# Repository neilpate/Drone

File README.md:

# Drone

A learning project: build a quadcopter from scratch — own hardware, own firmware, no existing flight stack.

The drone is the artefact; understanding the whole stack end-to-end is the deliverable.

## What we're building

- **Platform:** BBC micro:bit v2 (nRF52833) for Phases 1–3; custom nRF5340 PCBA for Phases 4–5.
- **Language:** Rust (`no_std`, `embassy-nrf`) on the firmware; Rust on the PC-side ground-station application too.
- **IMU:** ICM-42688-P on SPI (external; micro:bit's onboard sensor has no gyro).
- **Airframe:** quadcopter.
- **Flight stack:** rolling our own — no PX4 / ArduPilot.

See [`doc/00-vision.md`](doc/00-vision.md) for the full vision and the phased milestone plan.

## Status

**Phase 2 (advanced prototyping) in progress.** The whole stack runs on hardware. The drone has made **first free flights** — brief untethered, self-levelling hops on its own battery under closed-loop control — with telemetry over a two-hop radio link and PID gains **tuned live from the ground station and now persisted to flash** ([ADR 0025](doc/decisions/0025-persist-control-parameters-flash.md)): tune, save, power-cycle, and the gains survive.

- **Round trip, ~100 Hz, ~25–30 ms.** The `groundstation` app sends four-axis pilot commands (sliders or a gamepad) over USB-CDC to a remote micro:bit, which relays to the drone over IEEE 802.15.4 ([ADR 0014](doc/decisions/0014-radio-protocol-ieee802154.md)). Telemetry returns the same path as a high/low-rate split frame ([ADR 0027](doc/decisions/0027-split-telemetry-high-low-rate.md)), postcard + COBS framed, every buffer sized at compile time from the shared types.
- **Firmware — an Embassy task graph.** A **supervisor** failsafe ([ADR 0017](doc/decisions/0017-supervisor-failsafe-state-machine.md)) is the sole publisher of motor commands: a five-state machine with a stick arm/disarm gesture, idle auto-disarm, and loss-of-link detection within ~100 ms.
- **Sense → estimate → control.** The ICM-42688-P IMU ([ADR 0003](doc/decisions/0003-imu-icm42688-spi.md)) is read over SPI at 1 kHz; a complementary filter ([ADR 0022](doc/decisions/0022-attitude-estimation-complementary-filter.md)) gives a roll/pitch estimate; a single-loop **angle-mode PID** ([ADR 0024](doc/decisions/0024-control-law-angle-mode-pd.md)) mixes it and the pilot command into a four-motor demand. IMU zeroing is re-runnable from the ground station; every gain is a runtime message, saveable to flash.
- **Actuation + ESC telemetry.** **DShot300** drives a 4-in-1 AM32 ESC ([parts list](hardware/electrical/parts-list.md)); each ESC's **KISS serial telemetry** — RPM, pack voltage, temperature — is read back over an idle-framed UART and logged.
- **Discipline.** Frames, signs and command newtypes are fixed in [ADR 0021](doc/decisions/0021-coordinate-frames-and-command-semantics.md); the pure logic (filter, controller, supervisor, wire types) is host-tested in `firmware-drone-core`.

The ground station plots and logs every signal live, times the round trip, pushes and saves PID gains, shows a live 3D view of the drone's attitude, and pairs with an offline `analyze` tool that turns a telemetry log into a legible flight report.

Recent tuning work — validating the integral term as a **centre-of-mass trim corrector**, balancing the airframe by the per-motor effort split, and re-zeroing out a one-directional drift — is consolidated into a new control-troubleshooting field guide ([doc/06-control-troubleshooting.md](doc/06-control-troubleshooting.md)).

**Phase 4 bring-up:** the custom nRF5340 flight controller (`drone_fc` v2, [ADR 0026](doc/decisions/0026-phase4-custom-pcba-nrf5340.md), [ADR 0028](doc/decisions/0028-fabricate-v2-board-pcbway.md)) is assembled, and **both cores now run the real firmware with the radio link working end to end**. The application core runs the flight-task port; the network core runs a raw 802.15.4 bridge; the two exchange frames over a hand-rolled shared-memory transport with IPC doorbells ([ADR 0029](doc/decisions/0029-multi-board-firmware-shared-library.md)). On hardware, the startup IPC loopback passes on both cores and command/telemetry traffic flows with the micro:bit remote. **Motor bench testing found a hardware fault on M1:** on the second board, the module's P0.03 (NFC2, pad 30) cannot be controlled — it reads high while driven low and does not drive the M1 net — while M2–M4 and P0.02 behave normally; the first board also shows an M1 fault (about 180 Ω to ground). Next: decide between module rework and moving M1 to a spare GPIO, raise the repeat same-pin failure with the vendor, then measure IPC round-trip latency and link-loss behavior, props off. See [hardware bring-up](hardware/electrical/README.md).

**Next (to finish Phase 2):** rebuild on the lighter next-generation frame — the previous flight frame was retired in a lost-control crash — with the IMU mounted near the centre of mass (which should cut the estimator lag at its source) and a fresh, softer re-tune; plus a firmware **power-limit** mode and the netted test enclosure ([doc/07-safety.md](doc/07-safety.md)). The micro:bit remains the tuning platform in parallel.

See [`doc/progress.md`](doc/progress.md) for the dated milestone history, [`doc/dev-environment.md`](doc/dev-environment.md) for the toolchain, and [`doc/decisions/`](doc/decisions/README.md) for the full decision history.

## Repository layout

- [`AGENTS.md`](AGENTS.md) — shared context file for AI coding assistants (Copilot, Claude, etc.). Read first.
- [`crates/`](crates/README.md) — Cargo workspace. `firmware-drone-microbit` (on-target binary), `firmware-drone-shared` (board-agnostic tasks/signals), and `firmware-drone-core` (host-testable logic).
- [`doc/`](doc/README.md) — design notes, vision, architecture, hardware/software/control docs.
- [`doc/02-architecture.md`](doc/02-architecture.md) — system architecture overview (two micro:bits, RF link, ground-station evolution).
- [`doc/decisions/`](doc/decisions/README.md) — Architecture Decision Records (ADRs).
- [`hardware/`](hardware/README.md) — mechanical (Fusion 360) and electrical (KiCad).

## Testing

Host-testable logic (wire types, the supervisor state machine, the ground-station helpers) is unit-tested and run with [cargo-nextest](https://nexte.st/):

```sh
cargo nextest run                                                 # workspace host crates
cargo nextest run --manifest-path crates/groundstation/Cargo.toml # the GUI crate
```

A tracked `pre-push` git hook runs the suite before every push, and [GitHub Actions](.github/workflows/ci.yml) runs `fmt` + `clippy` + tests on every push and pull request (the badge above). On-target firmware is exercised on hardware, not in CI. See [`doc/ci-and-testing.md`](doc/ci-and-testing.md) for the details and the one-time hook setup.

## Decisions so far

- [ADR 0001](doc/decisions/0001-platform-airframe-stack.md) — Real-hardware quadcopter, roll our own firmware, learning-first scope.
- [ADR 0002](doc/decisions/0002-mcu-and-language.md) — BBC micro:bit v2 + Rust for Phases 1–3.
- [ADR 0003](doc/decisions/0003-imu-icm42688-spi.md) — External IMU: ICM-42688-P on SPI.
- [ADR 0004](doc/decisions/0004-concurrency-embassy-channels.md) — Concurrency model: Embassy + channel-based actor pattern, no BSP.
- [ADR 0005](doc/decisions/0005-pc-software-language-rust.md) — PC-side software in Rust; shared `proto` crate for the wire protocol.
- [ADR 0006](doc/decisions/0006-mechanical-cad-fusion360.md) — Mechanical CAD: Fusion 360; commit `.f3d` source + `.stl` mesh (STEP dropped, amended 2026-07-09).
- [ADR 0007](doc/decisions/0007-testing-and-ci-strategy.md) — Testing and CI: unit-test everything possible, local-first feedback, `core`/`task` split, HIL deferred.
- [ADR 0008](doc/decisions/0008-repository-folder-layout.md) — Repository folder layout: `crates/`, `doc/`, `hardware/{mechanical,electrical}/`, all lowercase.
- [ADR 0009](doc/decisions/0009-workspace-bootstrap-and-crate-naming.md) — Workspace bootstrap from day one; `firmware-<role>` naming; `core`/`task` split realised as sibling crates.
- [ADR 0010](doc/decisions/0010-board-support-package.md) — Board Support Package layer: `board` module inside `firmware-drone`, Cargo-feature-selected, tasks take erased types.
- [ADR 0011](doc/decisions/0011-task-tracking-issues-and-batches.md) — Task tracking: GitHub Issues as canonical backlog, Projects board as view, labels as taxonomy, batched filing.
- [ADR 0012](doc/decisions/0012-lint-and-format-policy.md) — Lint and format policy: `main` stays `rustfmt`-clean and `clippy`-clean; suppressions require justification.
- [ADR 0013](doc/decisions/0013-async-communication-primitives.md) — Async inter-task communication: 2×2 rule over `Channel` / `Watch` / `Signal` / `PubSubChannel`.
- [ADR 0014](doc/decisions/0014-radio-protocol-ieee802154.md) — Radio link: IEEE 802.15.4 (raw PHY/MAC), channel 20.
- [ADR 0015](doc/decisions/0015-host-testing-no-std-crates.md) — Host-testable `no_std` crates: `cfg_attr(not(test), no_std)`, inline `mod tests`, `cargo test` honours `default-members`.
- [ADR 0016](doc/decisions/0016-newtype-per-physical-quantity.md) — Newtype per physical quantity for shared types: distinct newtypes per quantity, no shared `PercentageValue` base.
- [ADR 0017](doc/decisions/0017-supervisor-failsafe-state-machine.md) — Supervisor task as failsafe state machine: 4-state enum, tick-driven, pure logic in `firmware-drone-core`, supervisor is the sole publisher of motor commands.
- [ADR 0018](doc/decisions/0018-pc-link-uart-postcard-cobs.md) — PC ground-station link: USB-CDC virtual COM port to nRF52833 UART, 115 200 8N1, postcard + COBS framing (Proposed; first cut shipped with plain ASCII).
- [ADR 0019](doc/decisions/0019-airframe-class-3in-4s-printed.md) — Airframe and propulsion class: 3" ducted cinewhoop, 4S LiPo, 1507-class motors, DShot 4-in-1 ESC, fully 3D-printed PETG frame (Proposed).
- [ADR 0020](doc/decisions/0020-telemetry-aggregator-single-publisher.md) — Telemetry aggregator: a dedicated task is the sole publisher of `TelemetryState`, tick-sampling per-source `Watch`es at 100 Hz and owning frame-level fields.
- [ADR 0021](doc/decisions/0021-coordinate-frames-and-command-semantics.md) — Coordinate frames and command semantics: world NED + body FRD, right-hand sign conventions, angle (self-levelling) mode first, remote sends raw normalised stick deflections (Proposed).
- [ADR 0022](doc/decisions/0022-attitude-estimation-complementary-filter.md) — Attitude estimation: complementary filter for roll and pitch (fixed-gain accel/gyro blend); yaw stays rate-only; pure filter in `firmware-drone-core` (Proposed).
- [ADR 0023](doc/decisions/0023-motor-numbering-layout-rotation.md) — Motor numbering, layout, and rotation directions: quad-X, Betaflight numbering (M1 rear-right … M4 front-left), props-out rotation, with the derived mixer sign table (Proposed).
- [ADR 0024](doc/decisions/0024-control-law-angle-mode-pd.md) — Control law: single-loop PD per axis, angle mode for roll/pitch and rate mode for yaw, derivative on the measured gyro; a single-publisher controller stage the supervisor mixes in Armed (Proposed).
- [ADR 0025](doc/decisions/0025-persist-control-parameters-flash.md) — Persist control parameters to flash: log-structured parameter store in internal flash, disarmed-gated save-on-command from the ground station (Accepted).
- [ADR 0026](doc/decisions/0026-phase4-custom-pcba-nrf5340.md) — Phase 4 custom PCBA: nRF5340 module on a hand-designed KiCad carrier (Proposed).
- [ADR 0027](doc/decisions/0027-split-telemetry-high-low-rate.md) — Split telemetry into high-rate and low-rate frames: fast flight data + slower housekeeping (Proposed).
- [ADR 0028](doc/decisions/0028-fabricate-v2-board-pcbway.md) — Fabricate the v2 flight-controller board: turnkey PCBA on PCBWay (Proposed).

## Licence

Dual-licensed under either of:

- Apache License, Version 2.0 ([LICENSE-APACHE](LICENSE-APACHE) or <http://www.apache.org/licenses/LICENSE-2.0>)
- MIT license ([LICENSE-MIT](LICENSE-MIT) or <http://opensource.org/licenses/MIT>)

at your option.

Unless you explicitly state otherwise, any contribution intentionally submitted for inclusion in this work, as defined in the Apache-2.0 license, shall be dual-licensed as above, without any additional terms or conditions.

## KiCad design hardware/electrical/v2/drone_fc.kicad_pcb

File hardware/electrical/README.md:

# hardware/electrical/

Electrical and electronic design: schematics, PCB layout, fabrication outputs, wiring diagrams.

## SWD probe bench test

The [Pico SWD probe bring-up note](swd-probe-bringup.md) records the investigation
and links the preserved scope screenshot and raw waveform data.

The host-only Rust tool [swd-test](../../crates/swd-test/src/main.rs) checks outgoing
SWD electrical activity with the target board **disconnected**. It uses only the
standard library and calls the installed `probe-rs` executable.

- Connect CH1 to SWCLK, CH2 to SWDIO, and both probe grounds to probe-board GND.
- Match the scope's attenuation settings to the physical probe switches.
- Defaults: Rigol DHO804 at `192.168.2.30:5555`, CMSIS-DAP probe selector
  `2e8a:000c:E66594D0637D4534`. Optional positional arguments override these.
- Run from the repository root:
  `cargo run --manifest-path crates/swd-test/Cargo.toml`.
- The tool changes channel scales/coupling, timebase, acquisition, and trigger
  settings, captures both channels, and leaves the scope stopped.
- It checks low/high levels (1st/99th percentiles) against 3.3 V logic
  thresholds, transitions on both lines, and median SWCLK frequency against
  100 kHz (+/-20%), with at least 20 samples per period. SWDIO levels are
  measured over the clock-active window so long idle periods do not mask bits.
- It samples SWDIO on SWCLK rising edges and verifies the initial sequence:
  at least 50 high clocks, JTAG-to-SWD selection `0xE79E` (LSB first), another
  at least 50 high clocks, at least two low idle clocks, then DPIDR read request
  `0xA5` with valid start, stop, park, and even parity bits.
  Exit code 0 means all electrical and initial-sequence checks passed.
- A `probe-rs` no-target error is expected. A passing electrical test does not
  verify later transfers, target connectivity, or the absence of brief
  overshoot/ringing. The ACK-slot value is reported but is not a target
  acknowledgement with the target disconnected. Inspect edges on the scope
  separately.
- Validate the tool with `cargo test --manifest-path crates/swd-test/Cargo.toml`
  and `cargo clippy --manifest-path crates/swd-test/Cargo.toml --all-targets -- -D warnings`.

## Electrical design files

### Application-core firmware

The [nRF5340 app crate](../../crates/firmware-drone-nrf5340-app/Cargo.toml)
is a workspace member (ADR 0029) but builds separately from micro:bit firmware. It selects the
`nrf5340-app-s` Embassy HAL feature and targets the secure application core
with `thumbv8m.main-none-eabihf`.
Do not build it together with the micro:bit firmware: Cargo combines dependency
features within one build, and the two Embassy chip features are incompatible.
The repository's VS Code rust-analyzer settings focus on the app and scope
build-script and Clippy checks to it. The micro:bit and groundstation require
separate editor configuration when working on them.
Run Cargo from `crates/firmware-drone-nrf5340-app` so its local target/linker
configuration is loaded: `cargo build`, then `cargo clippy --bin firmware-drone-nrf5340-app -- -D warnings`.
The app starts the external high-frequency crystal and creates the BSP and
flight tasks. Before spawning tasks, it checks the radio-core IPC loopback.
Embassy's default debug configuration allows access and may write UICR
to disable application and secure debug protection. P0.03 is configured as
GPIO rather than NFC for motor M1. The app BSP hands P0.31 (the radio LED) to
the network core in `Board::new`, consuming its pin singleton so no app-core
driver can claim it.
`cargo run` requires probe-rs 0.32.0 or later on PATH, selects
`nRF5340_xxAA_APPONLY`, and flashes via the Pico at 100 kHz.
probe-rs 0.30.0 has a known nRF53 recovery bug (upstream PR 3701).
The app-only target avoids accessing the network core over SWD.
Board power and a stable TC2050 contact are required.

For the bare-metal motor-pin bench test, disconnect the ESC and power the board
separately. Run `cargo run --example motor-gpio-test` from the app crate. It
disables NFCT and drives M1 (P0.03) low then high, about 2 s each, with the
input buffer connected. The status LED shows the value read back from the pin,
so it should alternate in step with the drive; M1 should measure about 0 V and
3.3 V. If UICR still selects NFC pins, the LED stays on and the pins are not
configured. The test restores the UICR debug-protection settings at startup
without modifying UICR. Flash the normal app to restore DShot operation.

The v2 IMU mounting requires a 180-degree rotation about Y into the FRD body
frame: `(body_x, body_y, body_z) = (-sensor_x, sensor_y, -sensor_z)`, for both
accelerometer and gyro. Bench tilt and rotation checks confirmed this mapping
on 2026-11-12. The app BSP applies it during byte conversion, before calibration
or estimation. Level and stationary should read approximately `(0, 0, -1)` g.

The app status LED on P0.28 is active-high: the PCB connects its anode to the
GPIO and its cathode through a resistor to ground. It starts off and displays
the supervisor-state blink pattern. Repeated publications of the same state
do not restart the pattern; only a different state interrupts it.

### Network-core radio bridge

The [radio crate](../../crates/firmware-drone-nrf5340-radio/Cargo.toml) selects
the `nrf5340-net` Embassy feature and the `thumbv8m.main-none-eabi` Rust target
(the network core has no FPU). Build it separately from the other firmware by
running `cargo build` from `crates/firmware-drone-nrf5340-radio`. Its ELF links
to network flash at `0x01000000`. Its runner selects the full
`nRF5340_xxAA` target and the Pico probe; network-core debug access and flashing
were verified with the previous LED smoke-test images. The current image is
a raw 802.15.4 payload bridge; it depends on `nrf5340-ipc` but has no postcard
or `firmware-types` dependency. Its `board` module (`src/board.rs`) owns the
clock setup, radio interrupt binding and pin map, and exposes the radio, the
status LED on P0.31 and an `AppCoreInterface` wrapping the IPC endpoint. The
entry point creates the board and independently spawns `tasks::status_led` and
`tasks::remote_link`. The LED is a heartbeat, not an IPC-readiness indicator.
The remote-link task bridges raw payloads; startup probes from the app are
answered inside `nrf5340-ipc` and never reach it. Each task lives in its own
file under the radio crate's `src/tasks/`.

### Inter-core radio transport

Implemented 2026-11-12; **working on hardware**. After a power-cycle both LEDs
blink, the app logs `radio-core IPC loopback passed`, the network core logs
`app-core IPC probe answered`, and command/telemetry traffic flows with the
micro:bit remote on channel 20. Network was flashed first, then app, using
probe-rs 0.32.0 without chip-wide recovery. Both cores build and pass Clippy
separately; the queue has host tests:
`cargo test -p nrf5340-ipc` and
`cargo clippy -p nrf5340-ipc --all-targets -- -D warnings`.

- The concrete app BSP `RadioCoreInterface` lives alongside the other wrappers
  in `src/board/nrf5340.rs` and wraps `nrf5340-ipc`; the radio BSP's
  `AppCoreInterface` is its network-core counterpart. The micro:bit
  implementation is unchanged. Postcard and command dispatch stay on the app
  core; Embassy's radio `Packet` stays on the network core.
- Both linkers reserve `0x20070000..0x20080000`. The first 1076 bytes contain
  a version/magic word and two four-slot SPSC queues. Each slot contains a
  length and up to 125 payload bytes, packed into atomic `u32` words. The PHY
  header, CRC and LQI are not sent through IPC.
- The app holds the network core off, configures SPU RAM regions 56--63 as
  non-secure read/write, initializes both queues, configures IPC and releases
  the network core. The network domain is non-secure; no access to the rest of
  the app's RAM is granted. Both binaries check the linker region and the
  shared layout size.
- IPC channel/event 0 is reserved on both cores. A doorbell follows each
  enqueue/dequeue. Acquire/release publication and a `DMB` before notification
  order memory accesses. The interrupt wakes the local async waiter; the
  queue, not the event bit, determines whether data is available.
- At startup the app sends `drone-ipc-v1` through the real frame queues and
  waits up to two seconds for the echo. On success the app logs
  `radio-core IPC loopback passed`; a mismatch or timeout stops app startup.
  The network
  core has no startup phase or timeout: `nrf5340-ipc`'s network-side
  `Endpoint::receive` echoes the probe whenever one arrives (logging
  `app-core IPC probe answered`) and returns only other frames. Both halves of
  the handshake live in `nrf5340-ipc`; the probe bytes are private to it. Both
  log lines were observed on hardware on 2026-11-12.
- `receive()` returns the actual frame length and is cancellation-safe.
  `send()` means **queued**, not successfully transmitted over the air.
  A full app-to-net queue waits at most 50 ms; oversize payloads fail
  explicitly. A full net-to-app queue drops the incoming frame with a warning
  rather than blocking outgoing radio traffic. On-air send errors are logged
  on the network core; IPC does not add retries or delivery guarantees.
- Chip-temperature sampling was removed from the app. It logs the absence
  and seeds temperature with NaN, keeping the unchanged sensors aggregator
  and telemetry schema live without inventing a measurement.

Before hardware testing, disconnect motors or remove propellers. Use matching
app and network images, then cold-boot both cores; do not combine this app
with the old network LED-only image. An independent network-core reset or
reflash reattaches to the existing queues without panicking, and frames sent
by the app while it was down may be transmitted late. The app does not
re-probe, so restart the app (or power-cycle) to re-run the startup check.
A startup failure leaves the BSP's continuous motor
STOP frames running but does not verify physical motor behavior.

Remaining hardware acceptance: measure round-trip latency through the extra
IPC hop and test link-loss behavior props-off. Working command/telemetry
traffic is not flight-readiness evidence.

### Running each core

From the relevant crate directory, `cargo r` builds, flashes and monitors that
core with defmt RTT:

```powershell
cd crates\firmware-drone-nrf5340-app
cargo r
```

Or, starting from the repository root:

```powershell
cd crates\firmware-drone-nrf5340-radio
cargo r
```

The app uses the application-only probe-rs target; the radio uses the full
two-core target. Both runners were tested with the previous smoke-test images:
each printed its own boot message, and both images verified unchanged after
running the other core. Both LEDs blinked after a subsequent cold boot.
The current IPC/radio images were verified on hardware on 2026-11-12. Stop the
RTT monitor with Ctrl+C.

The radio runner requires a working app image to start and release the network
core. If probe-rs reports core 1 locked, check that the board is powered, the
app is running, and the TC2050 has good contact. Do not automatically grant an
erase: that message alone does not establish why access is unavailable.

### Flashing without an RTT console

The following Windows PowerShell commands build and flash one image at a time
using the Pico probe. They verify the written image and do not request a
chip-wide erase or permission to recover locked cores. Run from the repository
root. Only run `probe-rs download` if `cargo build` succeeds:

```powershell
cd crates\firmware-drone-nrf5340-app
cargo build
probe-rs download --chip nRF5340_xxAA_APPONLY --probe 2e8a:000c:E66594D0637D4534 --protocol swd --speed 100 --verify ..\..\target\thumbv8m.main-none-eabihf\debug\firmware-drone-nrf5340-app
```

For the network core, start from the repository root again:

```powershell
cd crates\firmware-drone-nrf5340-radio
cargo build
probe-rs download --chip nRF5340_xxAA --probe 2e8a:000c:E66594D0637D4534 --protocol swd --speed 100 --verify ..\..\target\thumbv8m.main-none-eabi\debug\firmware-drone-nrf5340-radio
```

After flashing either image, release the probe and power-cycle the board. The
app must run and release the network core before full-target access can work.
App flashing followed by verification of the unchanged network image, and
network flashing followed by verification of the unchanged app image, were
tested on the board. The TC2050 contact is intermittent: if SWD fails during
flashing, re-establish contact and verify or reflash the affected image.

The full target can report a core as locked when its debug access port is
unavailable. Recovery with `--allow-erase-all` can erase either core's image;
restore both images if recovery reports both cores locked. Do not use a
chip-wide erase to work around an access failure without first diagnosing it.
`probe-rs download` is distinct from `cargo run`: it does not start an RTT
console.

**Primary content (Phase 4 onwards):** custom nRF5340 carrier-board PCBA — the successor to the BBC micro:bit v2 for Phases 4–5 ([ADR 0002](../../doc/decisions/0002-mcu-and-language.md)).

**Tool:** KiCad (assumed, not yet ADR'd — decision lands with the Phase 4 PCBA design ADR).

**Expected committed file types:**

- `*.kicad_pro`, `*.kicad_sch`, `*.kicad_pcb`, `*.kicad_sym`, `*.kicad_mod` — KiCad project, schematic, board, symbol library, footprint library.
- `*.step` — 3D export of the assembled board, for mechanical fit checks against `hardware/mechanical/`.
- Fabrication outputs (Gerbers, drill files, BOM, pick-and-place) under a `fab/` subfolder per board revision, generated on tag.

**Naming:** by board, e.g. `flight-controller-rev-a/`, `flight-controller-rev-b/`. New revision = new folder, never overwrite.

## v2 Module Symbol

The custom `MDBT53_P1M` symbol in [v2/drone_fc_v2_symbols.kicad_sym](v2/drone_fc_v2_symbols.kicad_sym) includes all 65 module pads, checked against the [Raytac Rev. E datasheet](../../doc/hardware/%5BnRF5340%5D%20MDBT53-1M%20%26%20MDBT53-P1M_Ver.E%20spec.pdf), section 2.5 (pages 15-18). (2026-09-05)

- U3A retains the existing wired pin positions; U3B exposes the remaining GPIO; U3C exposes the regulator connections. These are units of one physical module, not separate components.
- GPIO pins use manufacturer names and bidirectional electrical types. Application functions belong on schematic net labels, not in the library pin names. Refer to the datasheet for fixed alternate functions such as analog inputs, NFC, crystal, QSPI, and high-speed SPI.
- Every unused pad has an explicit schematic no-connect. U3C follows normal-voltage LDO mode (section 8.1.1): VDD and VDDH are tied to 3.3 V, and DCCH, DCCD, DECD, DCC, and DECR are unconnected. Firmware must not enable DC/DC without the required external circuit.
- The library and schematic copies are synchronised. All pre-existing electrical connections were preserved when completing the symbol. The PCB and manufacturing outputs were not updated; the earlier schematic LED polarity correction remains separate from the manufactured board.

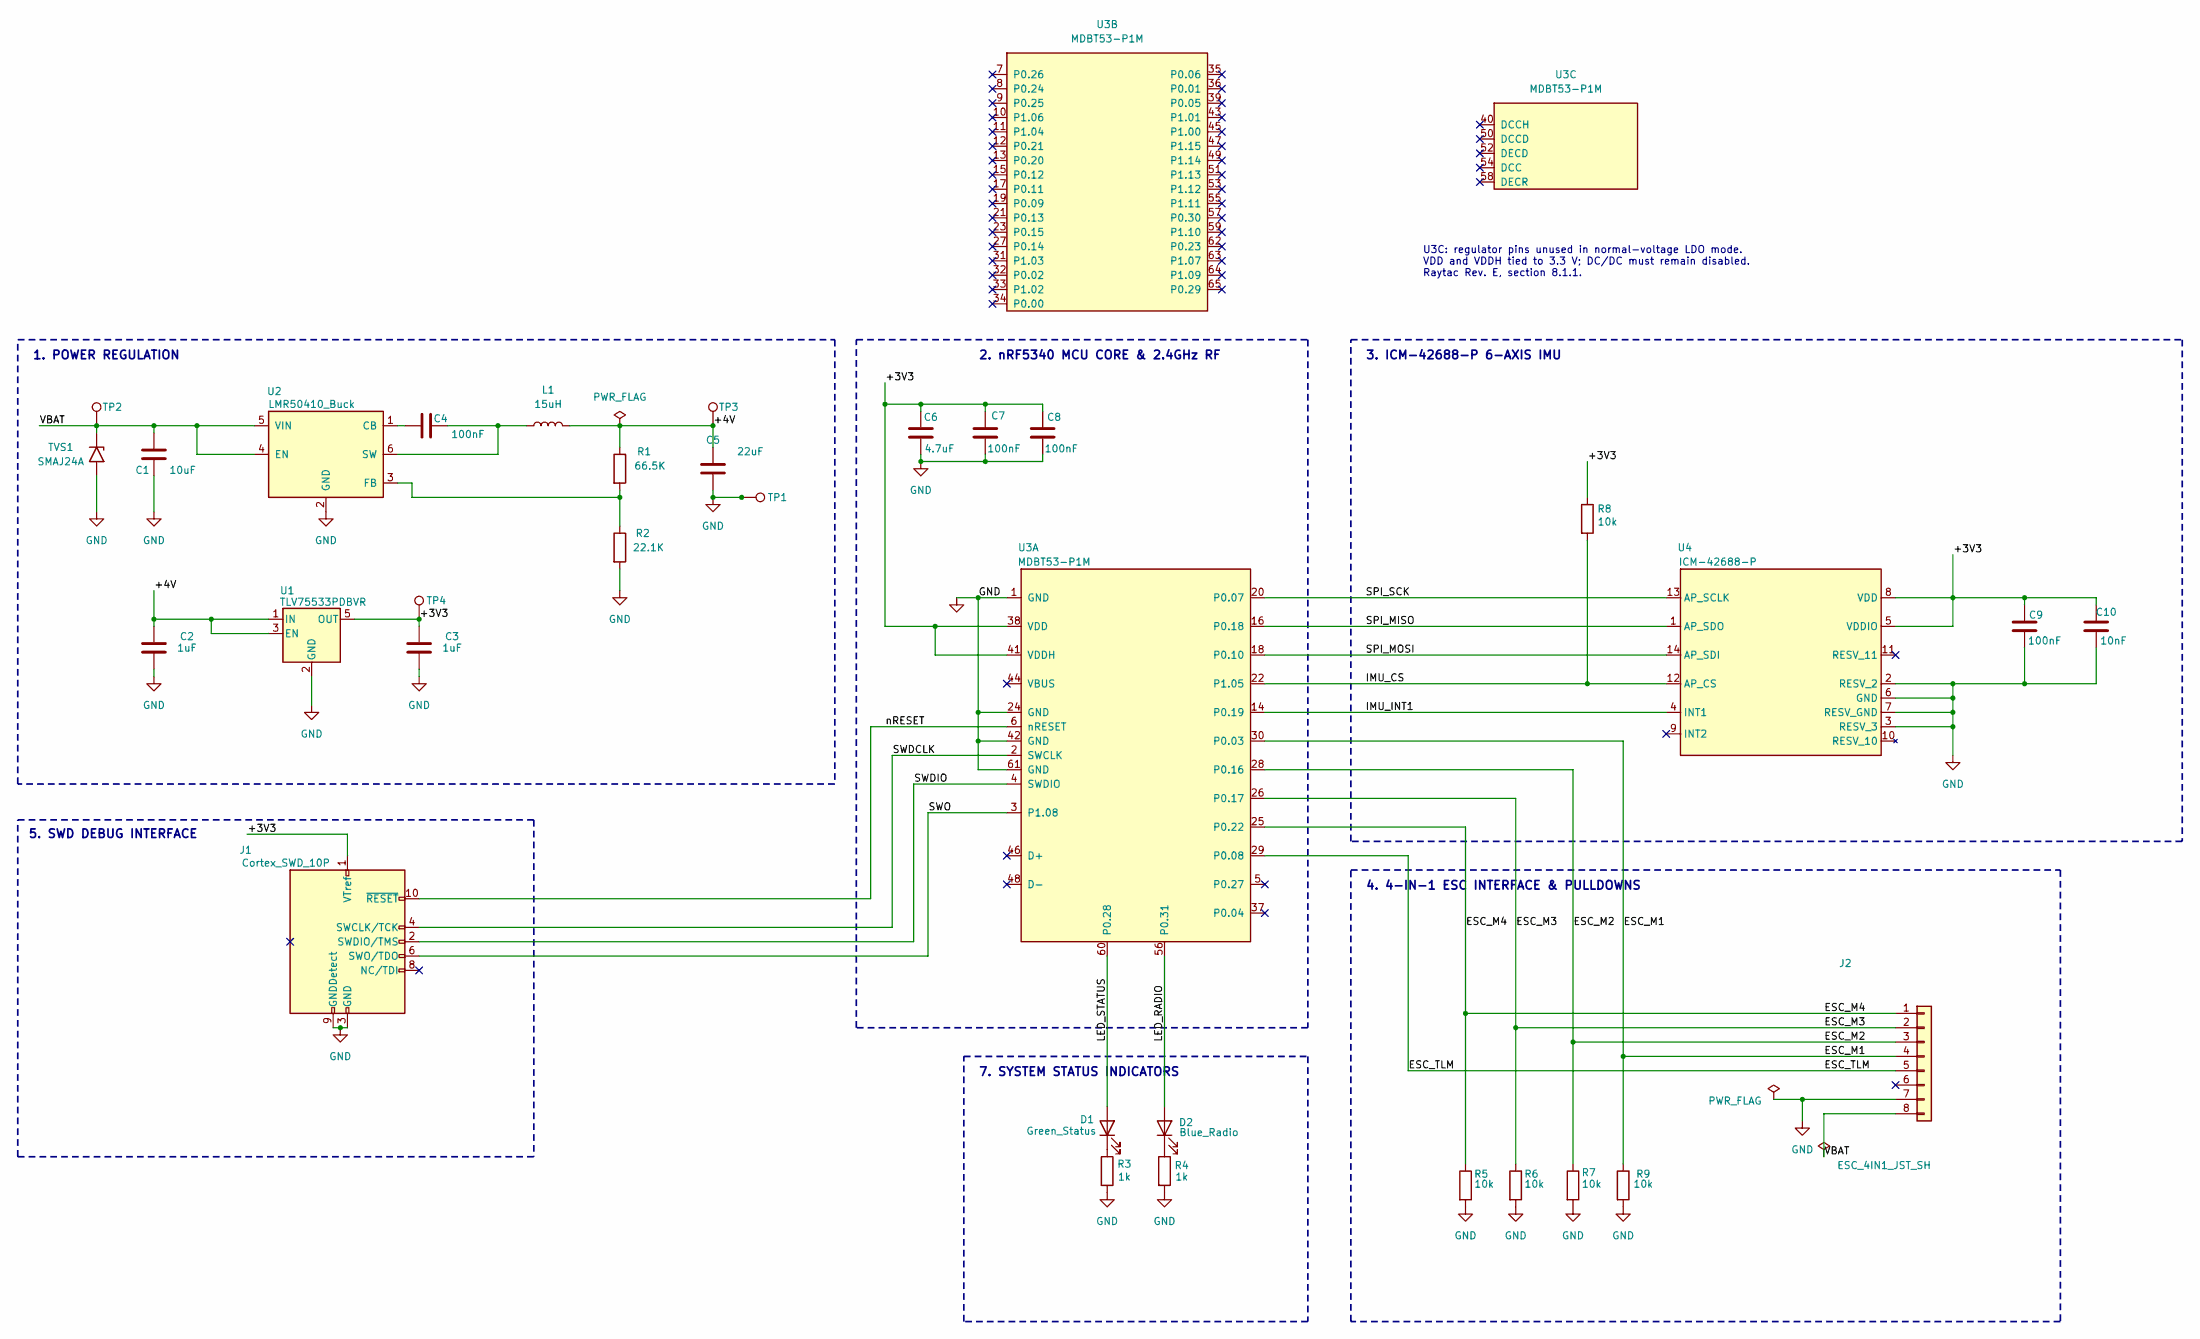
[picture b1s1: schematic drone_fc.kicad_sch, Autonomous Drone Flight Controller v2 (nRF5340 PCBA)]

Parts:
C1: 10uF; C_1206_3216Metric; MPN CL31B106KBHNNNE
C2, C3: 1uF; C_0402_1005Metric; MPN GRM155R61C105KA12D
C4, C7, C8, C9: 100nF; C_0402_1005Metric; MPN GRM155R71H104KE14D
C5: 22uF; C_0805_2012Metric; MPN GRM21BR61A226ME44
C6: 4.7uF; C_0603_1608Metric; MPN GRM188R61A475KAAJD
C10: 10nF; C_0402_1005Metric; MPN C0402C103K5RECAUTO
D1: Green_Status; LED_0402_1005Metric; MPN LTST-C281KGKT
D2: Blue_Radio; LED_0402_1005Metric; MPN LTST-C281TBKT
J1: Cortex_SWD_10P; Tag-Connect_TC2050-IDC-NL_2x05_P1.27mm_Vertical
J2: ESC_4IN1_JST_SH; JST_SH_SM08B-SRSS-TB_1x08-1MP_P1.00mm_Horizontal; MPN SM08B-SRSS-TB
L1: 15uH; L_0805_2012Metric; MPN MLZ2012M150WT000
R1: 66.5K; R_0402_1005Metric; MPN RC0402FR-0766K5L
R2: 22.1K; R_0402_1005Metric; MPN RC0402FR-0722K1L
R3, R4: 1k; R_0402_1005Metric; MPN RC0402FR-071KL
R5, R6, R7, R8, R9: 10k; R_0402_1005Metric; MPN RC0402FR-0710KL
TP1: GND; TestPoint_Pad_D1.0mm
TP2: VBAT; TestPoint_Pad_D1.0mm
TP3: +4V; TestPoint_Pad_D1.0mm
TP4: +3V3; TestPoint_Pad_D1.0mm
TVS1: SMAJ24A; D_SMA; MPN SMAJ24A
U1: TLV75533PDBVR; SOT-23-5; MPN TLV75533PDBVR
U2: LMR50410_Buck; SOT-23-6; MPN LMR50410XDBVR
U3: MDBT53-P1M; MPN MDBT53-P1M
U4: ICM-42688-P; LGA-14_3x2.5mm_P0.5mm_LayoutBorder3x4y; MPN ICM-42688-P

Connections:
/+3V3: C3.1, C6.1, C7.1, C8.1, C9.1, C10.1, J1.1 (VTref), R8.1, TP4.1 (1_1), U1.5 (OUT), U3.38 (VDD), U3.41 (VDDH), U4.5 (VDDIO), U4.8 (VDD)
/+4V: C2.1, C5.1, L1.2, R1.1, TP3.1 (1_1), U1.1 (IN), U1.3 (EN)
/ESC_M1: J2.4, R9.1, U3.30 (P0.03)
/ESC_M2: J2.3, R7.1, U3.28 (P0.16)
/ESC_M3: J2.2, R6.1, U3.26 (P0.17)
/ESC_M4: J2.1, R5.1, U3.25 (P0.22)
/ESC_TLM: J2.5, U3.29 (P0.08)
/IMU_CS: R8.2, U3.22 (P1.05), U4.12 (AP_CS)
/IMU_INT1: U3.14 (P0.19), U4.4 (INT1)
/LED_RADIO: D2.2 (A), U3.56 (P0.31)
/LED_STATUS: D1.2 (A), U3.60 (P0.28)
/SPI_MISO: U3.16 (P0.18), U4.1 (AP_SDO)
/SPI_MOSI: U3.18 (P0.10), U4.14 (AP_SDI)
/SPI_SCK: U3.20 (P0.07), U4.13 (AP_SCLK)
/SWDCLK: J1.4 (SWCLK/TCK), U3.2 (SWCLK)
/SWDIO: J1.2 (SWDIO/TMS), U3.4 (SWDIO)
/SWO: J1.6 (SWO/TDO), U3.3 (P1.08)
/VBAT: C1.1, J2.8, TP2.1 (1_1), TVS1.1 (A1), U2.4 (EN), U2.5 (VIN)
/nRESET: J1.10 (~RESET), U3.6 (nRESET)
GND: C1.2, C2.2, C3.2, C5.2, C6.2, C7.2, C8.2, C9.2, C10.2, J1.3 (GND), J1.5 (GND), J1.9 (GNDDetect), J2.7, R2.2, R3.2, R4.2, R5.2, R6.2, R7.2, R9.2, TP1.1 (1_1), TVS1.2 (A2), U1.2 (GND), U2.2 (GND), U3.1 (GND), U3.24 (GND), U3.42 (GND), U3.61 (GND), U4.2 (RESV_2), U4.3 (RESV_3), U4.6 (GND), U4.7 (RESV_GND)
unnamed: D1.1 (K), R3.1
unnamed: D2.1 (K), R4.1
unnamed: C4.2, U2.1 (CB)
unnamed: R1.2, R2.1, U2.3 (FB)
unnamed: C4.1, L1.1, U2.6 (SW)

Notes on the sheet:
2. nRF5340 MCU CORE & 2.4GHz RF
5. SWD DEBUG INTERFACE
3. ICM-42688-P 6-AXIS IMU
4. 4-IN-1 ESC INTERFACE & PULLDOWNS
1. POWER REGULATION
7. SYSTEM STATUS INDICATORS
U3C: regulator pins unused in normal-voltage LDO mode. VDD and VDDH tied to 3.3 V; DC/DC must remain disabled. Raytac Rev. E, section 8.1.1.

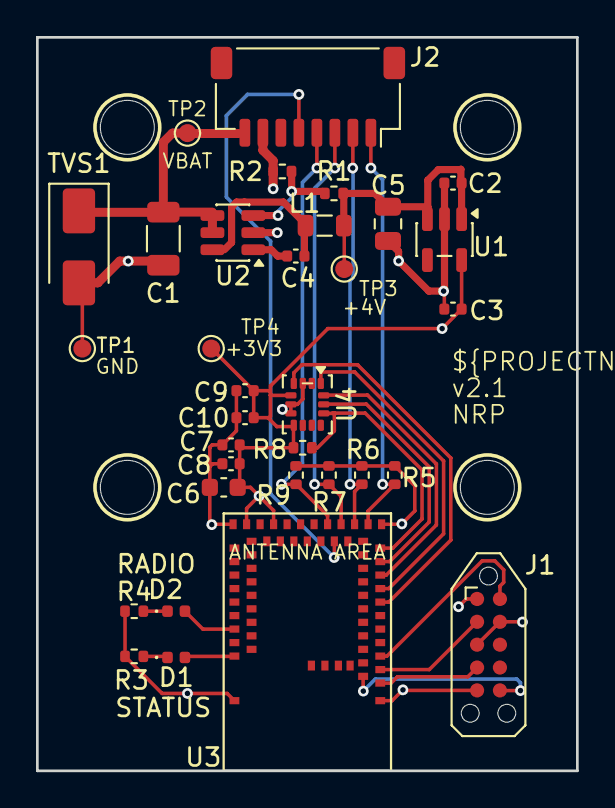
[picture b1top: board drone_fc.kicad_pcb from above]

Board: 4 copper layers, 30.0 x 40.8 mm, 37 parts (0 on the bottom side), 25 nets.

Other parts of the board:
H1, H2, H3, H4: M2 soft mount; MountingHole_3.0mm

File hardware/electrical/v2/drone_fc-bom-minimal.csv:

Comment,Designator,Footprint
10uF,C1,C_1206_3216Metric
1uF,"C2,C3",C_0402_1005Metric
100nF,"C4,C7,C8,C9",C_0402_1005Metric
22uF,C5,C_0805_2012Metric
4.7uF,C6,C_0603_1608Metric
10nF,C10,C_0402_1005Metric
Green_Status,D1,LED_0402_1005Metric
Blue_Radio,D2,LED_0402_1005Metric
Cortex_SWD_10P,J1,Tag-Connect_TC2050-IDC-NL_2x05_P1.27mm_Vertical
ESC_4IN1_JST_SH,J2,JST_SH_SM08B-SRSS-TB_1x08-1MP_P1.00mm_Horizontal
15uH,L1,L_0805_2012Metric
66.5K,R1,R_0402_1005Metric
22.1K,R2,R_0402_1005Metric
1k,"R3,R4",R_0402_1005Metric
10k,"R5,R6,R7,R8,R9",R_0402_1005Metric
SMAJ24A,TVS1,D_SMA
TLV75533PDBVR,U1,SOT-23-5
LMR50410_Buck,U2,SOT-23-6
MDBT53-P1M,U3,MDBT53-P1M
ICM-42688-P,U4,LGA-14_3x2.5mm_P0.5mm_LayoutBorder3x4y

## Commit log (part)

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2026-05-21 docs: add AGENTS.md as cross-assistant context file
2026-05-21 docs: flesh out top-level README
2026-05-23 docs: redefine phases (1-5, hardware-build oriented); add FPV plan
    Vision: replace the old 7-phase capability ladder (Phase 0 hello-world
    through Phase 6+ autonomy) with a 5-phase hardware-build plan and a
    'Beyond Phase 5' subsection. New phases:
    1 - single motor on bench (micro:bit, PWM, no battery)
    2 - four motors on bench (micro:bit, DShot, no battery)
    3 - first flights (micro:bit, battery, safety tether)
2026-05-23 docs: note rerun.io as plotter candidate; record ros2/gazebo as considered-and-rejected
    rerun.io added as the strong candidate for PC-side visualisation in
    both the vision open-questions list and the architecture open-
    questions list. New 'Considered and rejected' section in the
    architecture doc records why ROS2 and Gazebo-as-substitute were
    ruled out, so the trade-offs don't get relitigated.
2026-05-23 docs: clear stale info, fix failsafe deadline, refresh indexes
    Doc/README.md: full rewrite. Was still saying 'project just started,
    fill in vision next' from day one; now reflects that vision +
    architecture + 7 ADRs are in place. Marks unwritten domain docs
    explicitly with (not yet written). Promotes 07-safety.md as a Phase
    3 prerequisite. Resolves the 05 numbering clash by putting CI/dev-
    environment docs in unnumbered slots alongside the numbered domain
2026-05-23 docs(safety): tighten PPE to one hard rule, rest advisory
    Safety glasses stay mandatory whenever motors can spin. Closed-toe
    shoes, sleeve / jewellery / hair rules drop to sensible advice.
    A rule that gets ignored is worse than no rule; keeping the list
    short means the one rule that matters actually sticks.
    First-aid kit and phone-to-hand stay in their own bucket - they're
    lone-worker discipline, not PPE.
2026-05-23 chore: add .gitignore
    Standard Rust + VS Code + OS junk + Fusion 360 backup patterns.
    Cargo.lock is intentionally NOT ignored - this repo is binary
    crates, where Cargo.lock should be committed.
    VS Code config uses the keep-shared-ignore-personal pattern:
    ignore .vscode/* then unignore settings/tasks/launch/extensions
    so the workspace config can be checked in once the workspace lands.
2026-05-23 docs(agents): add 'prefer the idiomatic choice' working-style rule
    Where practical, do what someone fluent in the ecosystem would
    expect - Cargo conventions, Embassy patterns, standard crate /
    module / file naming, standard layouts. A stranger landing in
    the repo should not be surprised by how anything is done.
    Surprises are reserved for problem-specific decisions, recorded
    in an ADR. Picking a non-standard layout or naming scheme just
2026-05-23 docs(adr): add 0009 workspace bootstrap and crate naming
    Locks the three Phase-1 questions deferred by ADR 0008:
    1) firmware-<role> naming for on-target binaries
    (firmware-drone, firmware-ground, ...);
    2) core/task split realised as sibling crates
    (firmware-drone-core lib + firmware-drone bin) so
    the dependency graph enforces the no-HAL-in-core rule;
2026-05-23 chore(vscode): point rust-analyzer at thumbv7em target
    Mixed host/embedded workspace problem: rust-analyzer defaults
    to the host triple (x86_64-pc-windows-msvc) and complains that
    cortex-m ARM inline asm uses invalid registers (r0, r1) and
    missing symbols (__basepri_r etc). The cross-compile is fine;
    this is purely an editor-side analysis artefact.
    rust-analyzer.cargo.target = thumbv7em-none-eabihf matches what
2026-05-23 feat(firmware-drone): introduce board module with micro:bit v2 BSP
2026-05-23 docs(readme): update status to phase 1 in progress, list ADRs 0008-0010
2026-05-24 docs(adr): add 0011 task tracking - issues as backlog, batched filing
2026-05-24 refactor(firmware-drone): heartbeat task takes typed StatusLed handle
    Per ADR 0010, BSP hides wiring, tasks accept wrapper types.
    * board::StatusLed wraps the micro:bit v2 row/col matrix corner; on()/off() hide the charlieplexing.
    * Board::new constructs StatusLed eagerly.
    * heartbeat() is now board-agnostic; same source compiles against any board that exposes board::StatusLed.
    * Editor: rust-analyzer.check.command = `clippy` per ADR 0012.
    Closes #1
2026-05-24 feat(status): drive status LED from SystemState via Watch
    Replaces the fixed LED heartbeat with a SystemState-driven status indicator. A Watch<CriticalSectionRawMutex, SystemState, 8> publishes Booting/Idle/Fault; update_status_indicator subscribes and driv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
    First use of the embassy-sync pub/sub primitives codified in ADR 0013. SystemState lives in firmware-drone (not -core) because embassy-sync is forbidden in -core by ADR 0009; ADR 0013 still needs ame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
    main() cycles through the three
2026-05-25 feat(supervisor): introduce supervisor task as sole publisher of SystemState
    Moves SystemState and the STATUS Watch out of system_state.rs and into tasks/supervisor.rs alongside a new supervise task. Supervisor publishes Booting on startup, then for now cycles to Idle and Fau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
    STATUS and set() are private to the module so the supervisor is the only publisher; consumers go through pub fn subscribe() -> StatusReceiver instead of touching the static directly. status_led.rs up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
    main.rs no longer pokes SystemState directly; it just spawns the supervisor and status LED tasks. Docstring refresh
2026-05-25 docs(agents): record Windows PowerShell non-ASCII pipeline gotcha
    Round-tripping issue/PR bodies through PowerShell pipelines (e.g. gh issue view | Out-File | gh issue edit) corrupts non-ASCII characters via the legacy console code page. Rule recorded: write to a U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
2026-05-27 docs(adr): add 0014 radio protocol IEEE 802.15.4
    Records the choice of IEEE 802.15.4 (raw PHY/MAC, via embassy-nrf's
    ieee802154::Radio driver) for the drone <-> remote telemetry link.
    The original BLE-mode telemetry experiment for issue #5 hit two
    embassy-nrf BLE driver footguns (multi-address acceptance in
    RXADDRESSES, receive() completing on END rather than CRCOK). A
    follow-up experiment on branch experiment/ble-link-fixed (commit
2026-05-31 feat(motor): add motor BSP wrapper and demo task
    Adds L9110 H-bridge motor to the micro:bit v2 BSP (IA on P0.17, IB on P0.01) with forward/reverse/coast helpers. A new motor_controller task spins forward, coasts, then reverses on a fixed cycle as a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
    Scaffold only: GPIO toggling, not yet PWM. Direction-control is bench-useful for exercising both halves of the bridge, but a real quadcopter motor is single-direction (yaw via differential speed acro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
2026-06-01 feat(types): end-to-end throttle control via PilotCommand + Throttle
    Replace the placeholder ControlState with PilotCommand, the first real
    remote->drone wire type. PilotCommand carries a Throttle newtype (f32
    clamped to 0..=1, NaN-safe) and a sequence_count (transport concern
    that will move to a Frame<T> envelope later).
    firmware-types is split into per-type modules (pilot_command, throttle,
    telemetry_state) and gains postcard round-trip tests as a host-only
2026-06-01 docs(adr): add 0016 newtype per physical quantity
    Captures the rejected-DRY decision: every physical quantity gets its own newtype rather than sharing a PercentageValue / generic-bounded base. Headline reason is compile-time argument-order safety (m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
2026-06-05 feat(throttle): impl Mul<f32> for Throttle
    Operator overload routes through Throttle::from_normalised, so the
    clamp + NaN-scrub invariant is preserved when the multiplier overshoots
    the [0, 1] range.
    Needed by the supervisor's Degraded ramp-down: throttle * factor where
    factor goes from 1.0 to 0.0 across RAMP_TICKS ticks.
    Tests cover:
2026-06-09 feat(groundstation): add egui throttle slider over UART
    New host-only crate (binary 'gs') with a single egui slider that emits the throttle value as a decimal string + LF over a serial port at 115 200 8N1. Background thread owns the port, GUI thread sends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
2026-06-10 docs(learning): note GPIO-at-reset gotcha
    Captures the bench observation that the motor spun during firmware flashing, the underlying cause (nRF GPIOs are hi-Z at reset; active-low L9110 input reads that as `drive motor''), the two standard 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
2026-06-14 refactor(types): split per-role state enums into firmware-types
    Promote the drone supervisor's state enum and the remote's status enum
    to firmware-types as DroneState and RemoteState respectively. Each
    firmware now imports its own top-level state type rather than defining
    one inline in its signals/status.rs module, mirroring how MotorCommand,
    PilotCommand, Throttle and TelemetryState already live.
    Also finalises the per-module signals layout on the remote (status,
2026-06-14 refactor(firmware-drone): rename telemetry task to temperature
    The task reads the on-die TEMP sensor; 'telemetry' is the wire-payload concept (TelemetryState), not the task. Per-sensor naming keeps room for future sensor tasks (imu, baro) without overloading 'te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
2026-06-19 docs(learning): add embassy-time tickless timers and serial-link framing notes
2026-06-20 feat(groundstation): live telemetry plot with per-signal show/hide
    Route decoded TelemetryState from the serial thread to the UI and plot throttle, temperature and drone state as time series with egui_plot. Each signal has a show/hide checkbox; the serial thread req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
2026-06-20 docs(readme): add ground station screenshot of the 100 Hz round-trip plot
2026-06-20 ci(hooks): add pre-push hook running the host test suite
    Tracked .githooks/pre-push runs cargo test (workspace default-members)
    plus the host-only groundstation crate, so a green main no longer relies
    on remembering to run the tests. Enable once per clone with
    \git config core.hooksPath .githooks\. Document in doc/ci-and-testing.md.
2026-06-20 ci: add GitHub Actions workflow for host checks
    Run cargo fmt --check, clippy -D warnings and cargo nextest run on ubuntu-latest for every push to main and every PR. Scope is the host-testable workspace crates; on-target firmware and the groundsta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
2026-06-20 docs(readme): add Testing section covering nextest, hook and CI
2026-06-21 docs(images): add four-axis ground station screenshot
2026-06-22 telemetry: group sensor readings into a Sensors struct
    Nest the per-frame sensor values in a dedicated Sensors type instead of hanging temperature directly off TelemetryState, so adding IMU and other sensor channels later is a change to one struct rather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
    - firmware-types: new Sensors { temperature }, re-exported from the crate root; TelemetryState.temperature becomes TelemetryState.sensors.
    - telemetry aggregator builds Sensors from the temperature watch and publishes it in the frame.
    - add a firmware-drone sensors Watch signal for a future dedicated sensor source (not yet consumed).
2026-06-26 readme: note CPU-load profiler in status
2026-06-26 doc: note the postcard MaxSize bug surfaced only as the sequence counter grew
    The SerializeBufferFull panic was delayed because postcard varint-encodes the u32 sequence number: the frame fit under 32 bytes at boot and only overflowed once the counter widened past the LEB128 th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
2026-06-27 hook: mirror CI fmt and clippy gates in pre-push
    The pre-push hook only ran the test suite, so a formatting drift in firmware-remote pushed cleanly but failed CI on cargo fmt --all --check. Add the fmt and clippy gates for both scopes (workspace + 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
2026-06-27 imu: bring up ICM-42688 over SPI with raw 6-axis read
    Add check_identity (WHO_AM_I 0x47), configure (PWR_MGMT0 low-noise), and read_all (12-byte burst from ACCEL_DATA_X1) plus an ImuError type to the micro:bit BSP. Add the imu task that detects, configu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
    read_all currently performs the burst without parsing the bytes; scaling raw i16 counts to g/dps and a firmware-types IMU sample type follow next.
2026-06-27 groundstation: display IMU acceleration and angular rate
2026-06-27 imu: drop per-sample debug log of IMU data
